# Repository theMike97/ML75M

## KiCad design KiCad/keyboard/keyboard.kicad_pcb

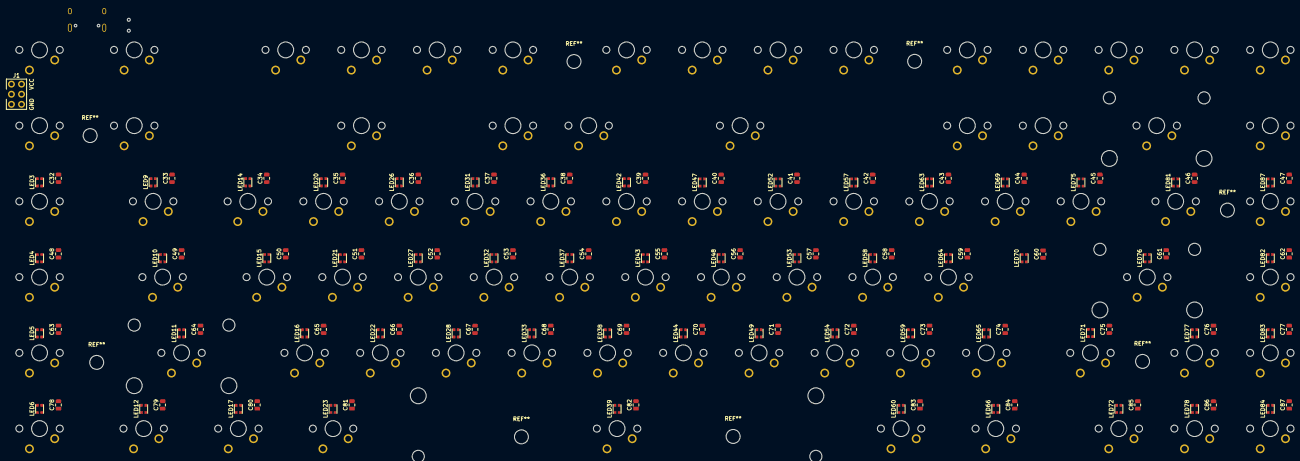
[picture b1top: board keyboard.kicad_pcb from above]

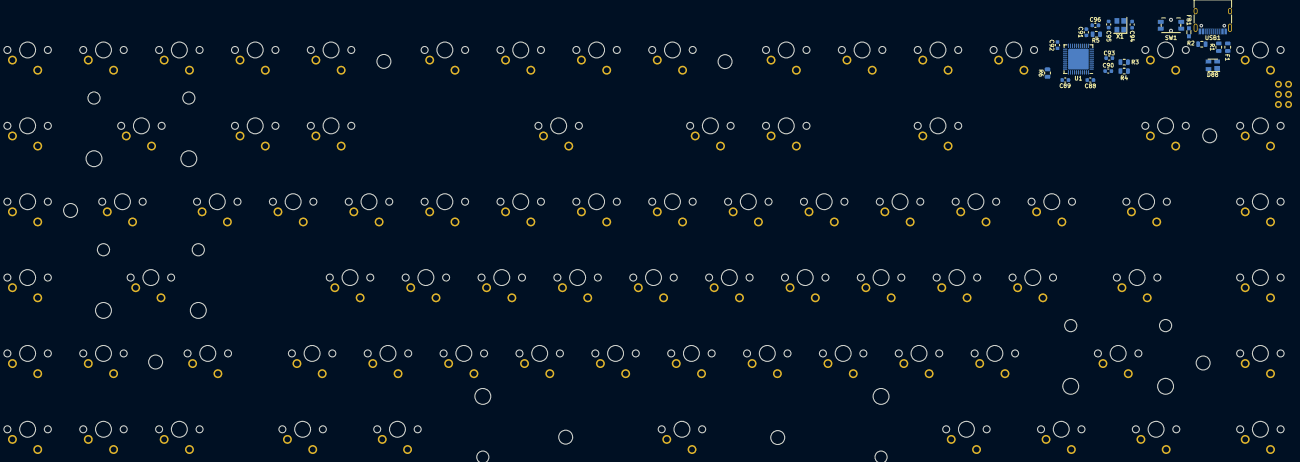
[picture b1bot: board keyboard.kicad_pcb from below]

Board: 2 copper layers, 216 parts (22 on the bottom side), 88 nets, no tracks yet.

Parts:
C32, C33, C34, C35, C36, C37, C38, C39, C40, C41, C42, C43, C44, C45, C46, C47, C48, C49, C50, C51, C52, C53, C54, C55, C56, C57, C58, C59, C60, C61, C62, C63, C64, C65, C66, C67, C68, C69, C70, C71, C72, C73, C74, C75, C76, C77, C78, C79, C80, C81, C82, C83, C84, C85, C86, C87: 100nF; C_0805_2012Metric
C88, C89, C90, C91: 100nF; C_0603_1608Metric
C92, C96: 10uF; C_0603_1608Metric
C93: 1uF; C_0603_1608Metric
C94, C95: 22pF; C_0603_1608Metric
D88: PRTR5V0U2X; SOT-143
F1: 1A hold, 2A trip; Fuse_0805_2012Metric
FB1: 60Ω@100MHz, 1A; Ferrite_SMD_0603
J1: AVR-ISP-6
LED3, LED4, LED5, LED6, LED9, LED10, LED11, LED12, LED14, LED15, LED16, LED17, LED20, LED21, LED22, LED23, LED26, LED27, LED28, LED31, LED32, LED33, LED36, LED37, LED38, LED39, LED42, LED43, LED44, LED47, LED48, LED49, LED52, LED53, LED54, LED57, LED58, LED59, LED60, LED63, LED64, LED65, LED66, LED69, LED70, LED71, LED72, LED75, LED76, LED77, LED78, LED81, LED82, LED83, LED84, LED87: WS2812B; WS2812B-2020
MX3, MX5, MX6, MX8, MX.>1: MX-LED; MXOnly-1U-NoLED
MX': MXOnly-1U-NoLED
MX-_1: MX-LED; MXOnly-1U-NoLED
MX/?1: MX-LED; MXOnly-1U-NoLED
MX;:1: MX-LED; MXOnly-1U-NoLED
MX=+1: MX-LED; MXOnly-1U-NoLED
MXA1: MX-LED; MXOnly-1U-NoLED
MXB1: MX-LED; MXOnly-1U-NoLED
MXBACK1: MX-LED; MXOnly-2U-ReversedStabilizers-NoLED
MXC1: MX-LED; MXOnly-1U-NoLED
MXCAPS1: MX-LED; MXOnly-1.75U-NoLED
MXD1: MX-LED; MXOnly-1U-NoLED
MXDEL1: MX-LED; MXOnly-1U-NoLED
MXDN1: MX-LED; MXOnly-1U-NoLED
MXE1: MX-LED; MXOnly-1U-NoLED
MXEND1: MX-LED; MXOnly-1U-NoLED
MXESC1: MX-NoLED; MXOnly-1U-NoLED
MXF1, MXF2, MXF3, MXF5: MX-NoLED; MXOnly-1U-NoLED
MXF4, MXF6, MXF7, MXF8, MXF9, MXF10, MXF11, MXF12, MXF13: MX-LED; MXOnly-1U-NoLED
MXFN1: MX-LED; MXOnly-1.25U-NoLED
MXG1: MX-LED; MXOnly-1U-NoLED
MXH1: MX-LED; MXOnly-1U-NoLED
MXHOME1: MX-LED; MXOnly-1U-NoLED
MXI1: MX-LED; MXOnly-1U-NoLED
MXJ1: MX-LED; MXOnly-1U-NoLED
MXK1: MX-LED; MXOnly-1U-NoLED
MXK,<1: MX-LED; MXOnly-1U-NoLED
MXL1: MX-LED; MXOnly-1U-NoLED
MXLALT1: MX-LED; MXOnly-1.25U-NoLED
MXLCTL1: MX-LED; MXOnly-1.25U-NoLED
MXLFT1: MX-LED; MXOnly-1U-NoLED
MXLSHFT1: MX-LED; MXOnly-2.25U-ReversedStabilizers-NoLED
MXM1: MX-NoLED; MXOnly-1U-NoLED
MXM2, MXM3, MXM4, MXM5, MXM6, MXM7: MX-LED; MXOnly-1U-NoLED
MXN1: MX-LED; MXOnly-1U-NoLED
MXO1: MX-LED; MXOnly-1U-NoLED
MXP1: MX-LED; MXOnly-1U-NoLED
MXPGDN1: MX-LED; MXOnly-1U-NoLED
MXPGUP1: MX-LED; MXOnly-1U-NoLED
MXQ1: MX-LED; MXOnly-1U-NoLED
MXR1: MX-LED; MXOnly-1U-NoLED
MXRALT1: MX-LED; MXOnly-1.25U-NoLED
MXRSHFT1: MX-LED; MXOnly-1.75U-NoLED
MXRT1: MX-LED; MXOnly-1U-NoLED
MXS1: MX-LED; MXOnly-1U-NoLED
MXSPACE1: MX-LED; MXOnly-6.25U-NoLED
MXT1: MX-LED; MXOnly-1U-NoLED
MXTAB1: MX-LED; MXOnly-1.5U-NoLED
MXTILDE1: MX-LED; MXOnly-1U-NoLED
MXU1: MX-LED; MXOnly-1U-NoLED
MXUP1: MX-LED; MXOnly-1U-NoLED
MXV1: MX-LED; MXOnly-1U-NoLED
MXW1: MX-LED; MXOnly-1U-NoLED
MXWIN1: MX-LED; MXOnly-1.25U-NoLED
MXX1: MX-LED; MXOnly-1U-NoLED
MXY1: MX-LED; MXOnly-1U-NoLED
MXZ1: MX-LED; MXOnly-1U-NoLED
MX[{1: MX-LED; MXOnly-1U-NoLED
MX\N1: MX-LED; MXOnly-2.25U-ReversedStabilizers-NoLED
MX\|1: MX-LED; MXOnly-1.5U-NoLED
MX]}1: MX-LED; MXOnly-1U-NoLED
R1, R2: 5.1kΩ; R_0805_2012Metric
R3, R4: 22Ω; R_0805_2012Metric
R5, R6: 10kΩ; R_0805_2012Metric
SW1: SW_Push; Panasonic_EVQPUM_EVQPUD
U1: ATmega32U4-MU; QFN-44-1EP_7x7mm_P0.5mm_EP5.2x5.2mm
USB1: USB_C_Receptacle_USB2.0; USB_C_Receptacle_HRO_TYPE-C-31-M-12
X1: 16MHz; Crystal_SMD_3225-4Pin_3.2x2.5mm

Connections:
+5V: C88.1, C89.1, C90.1, C91.1, C92.1, D88.4, F1.1, J1.2, R5.1, U1.2, U1.7, U1.14, U1.24, U1.34, U1.44
Col0: J1.1, MXM1.2, MXM2.2, MXM3.2, MXM4.2, MXM5.2, MXM6.2, U1.10
Col1: J1.3, MXCAPS1.2, MXESC1.2, MXLCTL1.2, MXLSHFT1.2, MXTAB1.2, MXTILDE1.2, U1.9
Col2: MXA1.2, MXQ1.2, MXWIN1.2, MXZ1.2, U1.41
Col3: MXF1.2, MXLALT1.2, MXS1.2, MXW1.2, MXX1.2, U1.32
Col4: MX3.2, MXC1.2, MXD1.2, MXE1.2, MXF2.2, U1.31
Col5: MXF3.2, MXF4.2, MXR1.2, MXV1.2, U1.30
Col6: MX5.2, MXB1.2, MXF5.2, MXG1.2, MXSPACE1.2, MXT1.2, U1.29
Col7: MX6.2, MXF6.2, MXH1.2, MXN1.2, MXY1.2, U1.28
Col8: MXF7.2, MXJ1.2, MXM7.2, MXU1.2, U1.27
Col9: MX8.2, MXF8.2, MXI1.2, MXK1.2, MXK,<1.2, U1.26
Col10: MX.>1.2, MXF9.2, MXL1.2, MXO1.2, MXRALT1.2, U1.25
Col11: MX/?1.2, MX;:1.2, MXF10.2, MXFN1.2, MXP1.2, U1.22
Col12: MX-_1.2, MXF11.2, MXLFT1.2, MXRSHFT1.2, MX[{1.2, U1.21
Col13: MX=+1.2, MXDN1.2, MXF12.2, MXUP1.2, MX\N1.2, MX]}1.2, U1.20
Col14: MXBACK1.2, MXF13.2, MXPGDN1.2, MXPGUP1.2, MXRT1.2, MX\|1.2, U1.19
Col15: MXDEL1.2, MXEND1.2, MXHOME1.2, U1.18
D+: D88.3, R3.2, USB1.A6, USB1.B6
D-: D88.2, R4.2, USB1.A7, USB1.B7
GND: C32.2, C33.2, C34.2, C35.2, C36.2, C37.2, C38.2, C39.2, C40.2, C41.2, C42.2, C43.2, C44.2, C45.2, C46.2, C47.2, C48.2, C49.2, C50.2, C51.2, C52.2, C53.2, C54.2, C55.2, C56.2, C57.2, C58.2, C59.2, C60.2, C61.2, C62.2, C63.2, C64.2, C65.2, C66.2, C67.2, C68.2, C69.2, C70.2, C71.2, C72.2, C73.2, C74.2, C75.2, C76.2, C77.2, C78.2, C79.2, C80.2, C81.2, C82.2, C83.2, C84.2, C85.2, C86.2, C87.2, C88.2, C89.2, C90.2, C91.2, C92.2, C93.2, C94.1, C95.1, C96.1, D88.1, FB1.1, J1.6, LED3.2, LED4.2, LED5.2, LED6.2, LED9.2, LED10.2, LED11.2, LED12.2, LED14.2, LED15.2, LED16.2, LED17.2, LED20.2, LED21.2, LED22.2, LED23.2, LED26.2, LED27.2, LED28.2, LED31.2, LED32.2, LED33.2, LED36.2, LED37.2, LED38.2, LED39.2, LED42.2, LED43.2, LED44.2, LED47.2, LED48.2, LED49.2, LED52.2, LED53.2, LED54.2, LED57.2, LED58.2, LED59.2, LED60.2, LED63.2, LED64.2, LED65.2, LED66.2, LED69.2, LED70.2, LED71.2, LED72.2, LED75.2, LED76.2, LED77.2, LED78.2, LED81.2, LED82.2, LED83.2, LED84.2, LED87.2, R1.1, R2.1, R6.1, SW1.1, U1.5, U1.15, U1.23, U1.35, U1.43, U1.45, USB1.A1, USB1.A12, USB1.B1, USB1.B12, X1.2, X1.4
LEDIN: J1.4, U1.11
unnamed: C32.1, C33.1, C34.1, C35.1, C36.1, C37.1, C38.1, C39.1, C40.1, C41.1, C42.1, C43.1, C44.1, C45.1, C46.1, C47.1, C48.1, C49.1, C50.1, C51.1, C52.1, C53.1, C54.1, C55.1, C56.1, C57.1, C58.1, C59.1, C60.1, C61.1, C62.1, C63.1, C64.1, C65.1, C66.1, C67.1, C68.1, C69.1, C70.1, C71.1, C72.1, C73.1, C74.1, C75.1, C76.1, C77.1, C78.1, C79.1, C80.1, C81.1, C82.1, C83.1, C84.1, C85.1, C86.1, C87.1, LED3.4, LED4.4, LED5.4, LED6.4, LED9.4, LED10.4, LED11.4, LED12.4, LED14.4, LED15.4, LED16.4, LED17.4, LED20.4, LED21.4, LED22.4, LED23.4, LED26.4, LED27.4, LED28.4, LED31.4, LED32.4, LED33.4, LED36.4, LED37.4, LED38.4, LED39.4, LED42.4, LED43.4, LED44.4, LED47.4, LED48.4, LED49.4, LED52.4, LED53.4, LED54.4, LED57.4, LED58.4, LED59.4, LED60.4, LED63.4, LED64.4, LED65.4, LED66.4, LED69.4, LED70.4, LED71.4, LED72.4, LED75.4, LED76.4, LED77.4, LED78.4, LED81.4, LED82.4, LED83.4, LED84.4, LED87.4
unnamed: C93.1, U1.6
unnamed: F1.2, USB1.A4, USB1.A9, USB1.B4, USB1.B9
unnamed: FB1.2, USB1.S1
unnamed: LED3.1, LED9.3
unnamed: LED4.3, LED87.1
unnamed: LED5.3, LED82.1
unnamed: LED6.3, LED83.1
unnamed: LED10.1, LED15.3
unnamed: LED4.1, LED10.3
unnamed: LED11.1, LED16.3
unnamed: LED5.1, LED11.3
unnamed: LED12.1, LED17.3
unnamed: LED6.1, LED12.3
unnamed: LED14.1, LED20.3
unnamed: LED9.1, LED14.3
unnamed: LED15.1, LED21.3
unnamed: LED16.1, LED22.3
unnamed: LED17.1, LED23.3
unnamed: LED20.1, LED26.3
unnamed: LED21.1, LED27.3
unnamed: LED22.1, LED28.3
unnamed: LED23.1, LED39.3
unnamed: LED26.1, LED31.3
unnamed: LED27.1, LED32.3
unnamed: LED28.1, LED33.3
unnamed: LED31.1, LED36.3
unnamed: LED32.1, LED37.3
unnamed: LED33.1, LED38.3
unnamed: LED36.1, LED42.3
unnamed: LED37.1, LED43.3
unnamed: LED38.1, LED44.3
unnamed: LED39.1, LED60.3
unnamed: LED42.1, LED47.3
unnamed: LED43.1, LED48.3
unnamed: LED44.1, LED49.3
unnamed: LED47.1, LED52.3
unnamed: LED48.1, LED53.3
unnamed: LED49.1, LED54.3
unnamed: LED52.1, LED57.3
unnamed: LED53.1, LED58.3
unnamed: LED54.1, LED59.3
unnamed: LED57.1, LED63.3
unnamed: LED58.1, LED64.3
unnamed: LED59.1, LED65.3
unnamed: LED60.1, LED66.3
unnamed: LED63.1, LED69.3
unnamed: LED64.1, LED70.3
unnamed: LED65.1, LED71.3
unnamed: LED66.1, LED72.3
unnamed: LED69.1, LED75.3
unnamed: LED70.1, LED76.3
unnamed: LED71.1, LED77.3
unnamed: LED72.1, LED78.3
unnamed: LED75.1, LED81.3
unnamed: LED76.1, LED82.3
unnamed: LED77.1, LED83.3
unnamed: LED78.1, LED84.3
unnamed: LED81.1, LED87.3
unnamed: R1.2, USB1.A5
unnamed: R2.2, USB1.B5
unnamed: R3.1, U1.4
unnamed: R4.1, U1.3
unnamed: R6.2, U1.33
Reset: C96.2, J1.5, R5.2, SW1.2, U1.13
XTAL1: C94.2, U1.17, X1.1
XTAL2: C95.2, U1.16, X1.3

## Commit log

2021-04-01 adding to github
2021-04-02 finishing led traces
2021-04-06 pcb almost finished, BOM generated
2021-04-08 added 6pin ISP to load bootloader
